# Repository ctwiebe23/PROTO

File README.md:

# NAME

MAKE --- PROTO's embedded python library

# DESCRIPTION

MAKE is Python library that runs on top of [CircuitPython][], creating an
interface for controlling sensors and motors connected to an RP2040-based PCB.

[circuitpython]: https://circuitpython.org/

The goal of the project is to create a simple-to-use library that can be
brought into elementary / middle schools and taught with minimal programming
experience on either side --- student *or* teacher.  It prioritizes readability
and simplicity over efficiency, and was designed under many constraints
imposed by the RP2040, CircuitPython, and its intended environment.

```py
import make

left_motor = make.largemotor(port=6)
right_motor = make.largemotor(port=7, direction=-1)
my_robot = make.drivetrain(left_motor, right_motor)

stop_button = make.button(port=8)

my_robot.drive(100)
make.wait_until(stop_button.pressed)
my_robot.stop()
```

# FUNCTIONS AND CLASSES

# INSTALL

MAKE must be installed on a system that already has CircuitPython set up. If
this is not the case, first follow this guide to [install
CircuitPython][install-circuitpython] on your board.  To determine if
CircuitPython has been installed, plug the board into your computer via a USB
--- the board should pop up in your file system as a USB device named
`CIRCUITPY`.

[install-circuitpython]: https://learn.adafruit.com/welcome-to-circuitpython/installing-circuitpython

Once CircuitPython is working and you have found the `CIRCUITPY` drive, enter
it and copy the `./src/lib` folder from this Github repository to the drive.
This folder (`CIRCUITPY/lib`) is where CircuitPython searches for libraries,
and the `./src/lib` folder in the repo contains everything MAKE needs ---
well, almost.

Depending on your board, additional libraries may need to be installed ---
these can be found in `./src/component_libraries`.  The only such library that
is currently needed is the Adafruit motor library --- if your board is the
[MakerPI RP2040][makerpi], this comes pre-installed, but otherwise you likely
will need to copy `./src/component_libraries/adafruit_motor` into
`CIRCUITPY/lib`.

[makerpi]: https://www.cytron.io/p-maker-pi-rp2040-simplifying-robotics-with-raspberry-pi-rp2040

The final step to get code running is to place a `main.py` file at the root of
`CIRCUITPY`.  This is the file that CircuitPython will run when the board
starts up, and is where you will write the "main method" for your program.  To
upload a new program, simply overwrite `CIRCUITPY/main.py`.

# EXAMPLES

# INDEX

CHANGELOG.md
:   foo

justfile
:   foo

LICENSE
:   foo

pyproject.toml
:   foo

README.md
:   This file.

data/
:   foo

doc/
:   foo

    fonts.html
    :   foo

    pandoc.yml
    :   foo

    source.md
    :   foo

    styles.css
    :   foo

    www/
    :   foo

    tutorial_pages/
    :   foo

        example_code/
        :   foo

src/
:   foo

    main.py
    :   foo

    component_libraries/
    :   foo

    lib/
    :   foo

        make.py
        :   foo

        proto/
        :   foo

            \*/\_\_init\_\_.py
            :   foo

            system.py
            :   foo

            general/
            :   foo

            input/
            :   foo

            motion/
            :   foo

            schemata/
            :   foo

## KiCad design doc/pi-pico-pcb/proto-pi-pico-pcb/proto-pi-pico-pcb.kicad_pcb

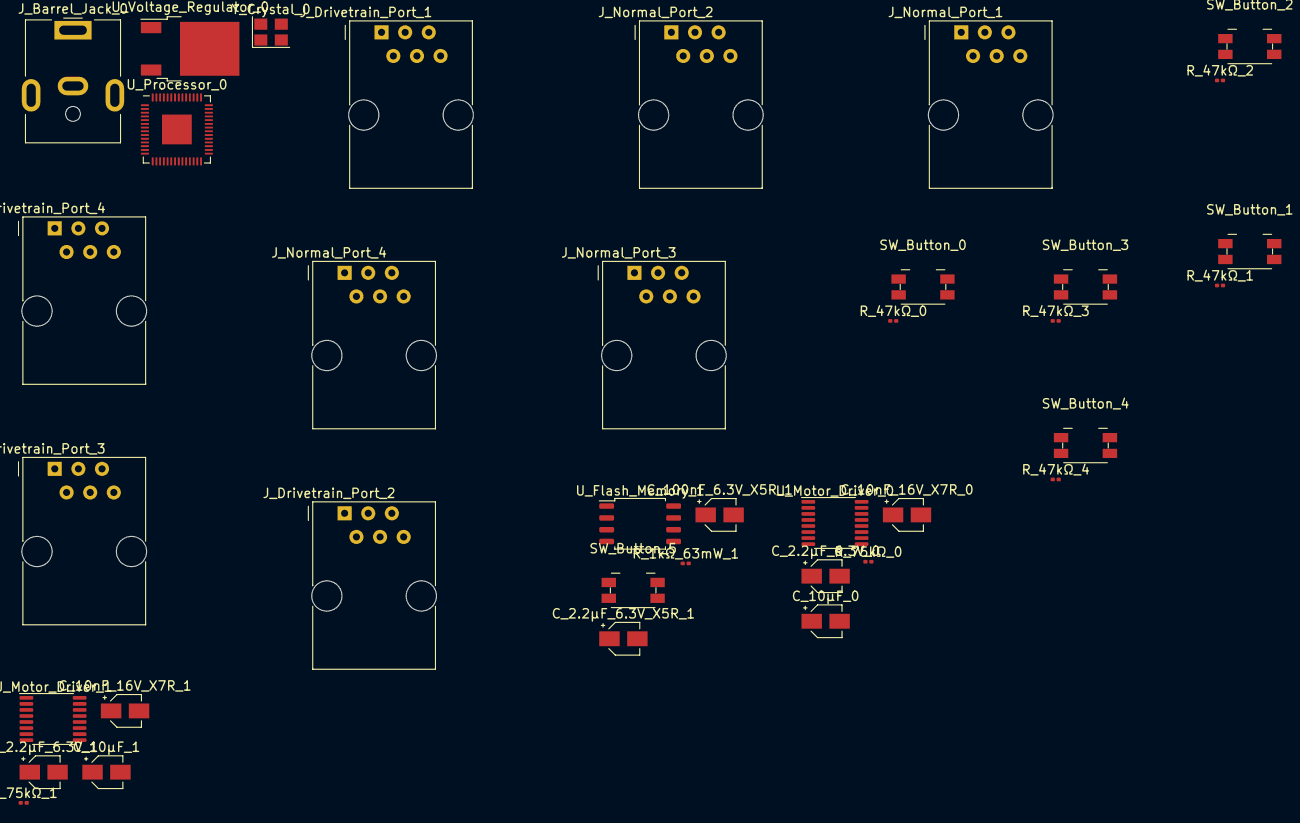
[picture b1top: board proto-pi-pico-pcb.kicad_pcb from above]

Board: 2 copper layers, 37 parts (0 on the bottom side), 52 nets, no tracks yet.

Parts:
C_2.2μF_6.3V_0, C_2.2μF_6.3V_1, C_2.2μF_6.3V_X5R_1, C_10nF_16V_X7R_0, C_10nF_16V_X7R_1, C_10μF_0, C_10μF_1, C_100nF_6.3V_X5R_1: C; CP_Elec_3x5.3
J_Barrel_Jack_0: Barrel_Jack_MountingPin; BarrelJack_CUI_PJ-063AH_Horizontal
J_Drivetrain_Port_1, J_Drivetrain_Port_2, J_Drivetrain_Port_3, J_Drivetrain_Port_4: 6P6C; RJ12_Amphenol_54601
J_Normal_Port_1, J_Normal_Port_2, J_Normal_Port_3, J_Normal_Port_4: 6P6C; RJ12_Amphenol_54601
R_1kΩ_63mW_1, R_47kΩ_0, R_47kΩ_1, R_47kΩ_2, R_47kΩ_3, R_47kΩ_4, R_75kΩ_0, R_75kΩ_1: R; R_0201_0603Metric
SW_Button_0, SW_Button_1, SW_Button_2, SW_Button_3, SW_Button_4, SW_Button_5: SW_Push; Panasonic_EVQPUJ_EVQPUA
U_Flash_Memory_1: W25Q32JVSS; SOIC-8_5.23x5.23mm_P1.27mm
U_Motor_Driver_0, U_Motor_Driver_1: DRV8833PW; TSSOP-16_4.4x5mm_P0.65mm
U_Processor_0: RP2040; QFN-56-1EP_7x7mm_P0.4mm_EP3.2x3.2mm
U_Voltage_Regulator_0: KA78M05_TO252; TO-252-2
Y_Crystal_0: Crystal; Crystal_SMD_Abracon_ABM8G-4Pin_3.2x2.5mm

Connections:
+3.3V: C_2.2μF_6.3V_X5R_1.2, C_100nF_6.3V_X5R_1.2, J_Drivetrain_Port_1.2, J_Drivetrain_Port_2.2, J_Drivetrain_Port_3.2, J_Drivetrain_Port_4.2, J_Normal_Port_1.2, J_Normal_Port_2.2, J_Normal_Port_3.2, J_Normal_Port_4.2, R_47kΩ_0.1, R_47kΩ_1.1, R_47kΩ_2.1, R_47kΩ_3.1, R_47kΩ_4.1, U_Flash_Memory_1.8 (VCC), U_Processor_0.1 (IOVDD), U_Processor_0.10 (IOVDD), U_Processor_0.22 (IOVDD), U_Processor_0.33 (IOVDD), U_Processor_0.42 (IOVDD), U_Processor_0.43 (ADC_AVDD), U_Processor_0.44 (VREG_IN), U_Processor_0.48 (USB_VDD), U_Processor_0.49 (IOVDD), U_Voltage_Regulator_0.3 (VO)
+9V: C_10nF_16V_X7R_0.1, C_10nF_16V_X7R_1.1, C_10μF_0.1, C_10μF_1.1, J_Barrel_Jack_0.1, R_75kΩ_0.1, R_75kΩ_1.1, U_Motor_Driver_0.12 (VM), U_Motor_Driver_1.12 (VM), U_Voltage_Regulator_0.1 (VI)
/Drivetrain_Port_0/DC_0: J_Drivetrain_Port_4.5, U_Motor_Driver_0.2 (AOUT1)
/Drivetrain_Port_0/DC_1: J_Drivetrain_Port_4.6, U_Motor_Driver_0.4 (AOUT2)
/Drivetrain_Port_1/DC_0: J_Drivetrain_Port_1.5, U_Motor_Driver_0.7 (BOUT1)
/Drivetrain_Port_1/DC_1: J_Drivetrain_Port_1.6, U_Motor_Driver_0.5 (BOUT2)
/Drivetrain_Port_2/DC_0: J_Drivetrain_Port_3.5, U_Motor_Driver_1.2 (AOUT1)
/Drivetrain_Port_2/DC_1: J_Drivetrain_Port_3.6, U_Motor_Driver_1.4 (AOUT2)
/Drivetrain_Port_3/DC_0: J_Drivetrain_Port_2.5, U_Motor_Driver_1.7 (BOUT1)
/Drivetrain_Port_3/DC_1: J_Drivetrain_Port_2.6, U_Motor_Driver_1.5 (BOUT2)
/Flash_Memory_0/!CS: R_1kΩ_63mW_1.2, U_Flash_Memory_1.1 (~CS), U_Processor_0.56 (QSPI_SS)
/Flash_Memory_0/CLK: U_Flash_Memory_1.6 (CLK), U_Processor_0.52 (QSPI_SCLK)
/Flash_Memory_0/IO_0: U_Flash_Memory_1.5 (DI(IO0)), U_Processor_0.53 (QSPI_SD0)
/Flash_Memory_0/IO_1: U_Flash_Memory_1.2 (DO(IO1)), U_Processor_0.55 (QSPI_SD1)
/Flash_Memory_0/IO_2: U_Flash_Memory_1.3 (IO2), U_Processor_0.54 (QSPI_SD2)
/Flash_Memory_0/IO_3: U_Flash_Memory_1.7 (IO3), U_Processor_0.51 (QSPI_SD3)
/GP_0: R_47kΩ_0.2, SW_Button_0.2, U_Processor_0.37 (GPIO25)
/GP_1: R_47kΩ_1.2, SW_Button_1.2, U_Processor_0.36 (GPIO24)
/GP_2: R_47kΩ_2.2, SW_Button_2.2, U_Processor_0.35 (GPIO23)
/GP_3: R_47kΩ_3.2, SW_Button_3.2, U_Processor_0.34 (GPIO22)
/GP_4: J_Normal_Port_1.4, U_Processor_0.32 (GPIO21)
/GP_5: J_Normal_Port_2.4, U_Processor_0.31 (GPIO20)
/GP_6: J_Normal_Port_3.4, U_Processor_0.30 (GPIO19)
/GP_7: J_Normal_Port_4.4, U_Processor_0.29 (GPIO18)
/GP_8: J_Drivetrain_Port_4.3, U_Processor_0.28 (GPIO17)
/GP_9: J_Drivetrain_Port_4.4, U_Processor_0.27 (GPIO16)
/GP_10: J_Drivetrain_Port_1.3, U_Processor_0.18 (GPIO15)
/GP_11: J_Drivetrain_Port_1.4, U_Processor_0.17 (GPIO14)
/GP_12: J_Drivetrain_Port_3.3, U_Processor_0.16 (GPIO13)
/GP_13: J_Drivetrain_Port_3.4, U_Processor_0.15 (GPIO12)
/GP_14: J_Drivetrain_Port_2.3, U_Processor_0.14 (GPIO11)
/GP_15: J_Drivetrain_Port_2.4, U_Processor_0.13 (GPIO10)
/Motor_Driver_0/A_IN_0: U_Motor_Driver_0.16 (AIN1), U_Processor_0.12 (GPIO9)
/Motor_Driver_0/A_IN_1: U_Motor_Driver_0.15 (AIN2), U_Processor_0.11 (GPIO8)
/Motor_Driver_0/B_IN_0: U_Motor_Driver_0.9 (BIN1), U_Processor_0.9 (GPIO7)
/Motor_Driver_0/B_IN_1: U_Motor_Driver_0.10 (BIN2), U_Processor_0.8 (GPIO6)
/Motor_Driver_1/A_IN_0: U_Motor_Driver_1.16 (AIN1), U_Processor_0.7 (GPIO5)
/Motor_Driver_1/A_IN_1: U_Motor_Driver_1.15 (AIN2), U_Processor_0.6 (GPIO4)
/Motor_Driver_1/B_IN_0: U_Motor_Driver_1.9 (BIN1), U_Processor_0.5 (GPIO3)
/Motor_Driver_1/B_IN_1: U_Motor_Driver_1.10 (BIN2), U_Processor_0.4 (GPIO2)
/RESET_Button_0/SIGNAL: R_47kΩ_4.2, SW_Button_4.2, U_Processor_0.26 (RUN)
GND: C_2.2μF_6.3V_0.1, C_2.2μF_6.3V_1.1, C_2.2μF_6.3V_X5R_1.1, C_10μF_0.2, C_10μF_1.2, C_100nF_6.3V_X5R_1.1, J_Barrel_Jack_0.2, J_Drivetrain_Port_1.1, J_Drivetrain_Port_2.1, J_Drivetrain_Port_3.1, J_Drivetrain_Port_4.1, J_Normal_Port_1.1, J_Normal_Port_2.1, J_Normal_Port_3.1, J_Normal_Port_4.1, SW_Button_0.1, SW_Button_1.1, SW_Button_2.1, SW_Button_3.1, SW_Button_4.1, SW_Button_5.2, U_Flash_Memory_1.4 (GND), U_Motor_Driver_0.3 (AISEN), U_Motor_Driver_0.6 (BISEN), U_Motor_Driver_0.13 (GND), U_Motor_Driver_1.3 (AISEN), U_Motor_Driver_1.6 (BISEN), U_Motor_Driver_1.13 (GND), U_Processor_0.19 (TESTEN), U_Processor_0.57 (GND), U_Voltage_Regulator_0.2 (GND)
unnamed: C_2.2μF_6.3V_0.2, U_Motor_Driver_0.14 (VINT)
unnamed: C_2.2μF_6.3V_1.2, U_Motor_Driver_1.14 (VINT)
unnamed: C_10nF_16V_X7R_0.2, U_Motor_Driver_0.11 (VCP)
unnamed: C_10nF_16V_X7R_1.2, U_Motor_Driver_1.11 (VCP)
unnamed: R_1kΩ_63mW_1.1, SW_Button_5.1
unnamed: R_75kΩ_0.2, U_Motor_Driver_0.1 (nSLEEP)
unnamed: R_75kΩ_1.2, U_Motor_Driver_1.1 (nSLEEP)
unnamed: U_Processor_0.20 (XIN), Y_Crystal_0.1
unnamed: U_Processor_0.21 (XOUT), Y_Crystal_0.2
unnamed: U_Processor_0.23 (DVDD), U_Processor_0.45 (VREG_VOUT), U_Processor_0.50 (DVDD)

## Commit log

2024-03-21 created utility file
2024-03-27 changed to class structure
2024-03-30 formatting
2024-04-05 created pause_until and changed formatting
2024-04-05 started documentation
2024-04-05 setup readme pages
2024-04-06 tweaking of formatting
2024-04-10 declaring as of yet unused variables
2024-04-11 established good practice
2024-04-11 testing git log
2024-04-16 redid download link
2024-04-16 undid prev change
2024-04-17 documentation
2024-04-17 filled out readme and formatted pages
2024-04-17 fixed Callable error
2024-04-17 renamed dc to motor
2024-04-17 victor demo
2024-04-17 04/17 meeting
2024-04-17 naming convention
2024-04-17 fixed error
2024-04-18 added largemotor.stop
2024-04-18 removed whitespace
2024-04-22 documentation work
2024-04-22 setting up stopall
2024-04-22 translated techdoc to markdown
2024-04-25 begun transfer from md to tex
2024-04-29 cleaned up
2024-04-29 added todo and stl's
2024-04-29 translated techdoc to latex for real this time
2024-04-29 added MaKeTeX.sh
2024-05-01 finished servo
2024-05-03 rearranging
2024-05-08 documentation preparation
2024-05-08 fixed typo
2024-05-08 folder restructering
2024-05-08 added grove ports
2024-05-08 structering
2024-05-09 3d printed insert tester
2024-05-09 little bit of expirementing
2024-05-09 typo
2024-05-09 reorganized file structure to reflect pi
2024-05-09 fixed regex issue
2024-05-09 updated todo
2024-05-09 covered edge case
2024-05-11 removed will
2024-05-13 updated prints and renamed folders
2024-05-14 finished drivetrain, configured presentation code
2024-05-14 made presentation code
2024-05-16 presentation practice
2024-05-16 final presentation change
2024-05-21 added additional todo
2024-06-04 gave drivetrain alt constructors and revamped BAPCAT warning
2024-06-04 added to todo
2024-06-04 reformatting
2024-06-04 cleaned whitespace
2024-06-05 formating
2024-06-23 restructured BAPCAT to limit cat abuse
2024-06-30 cleared whitespace
2024-07-05 redid bapcat
2024-07-19 refactoring BAPCAT
2024-07-19 held BAPCAT to a higher standard
2024-07-20 renamed motors + drivetrain
2024-07-20 major reformatting and proofreading
2024-07-21 documented small_motor
2024-07-24 removec camelCasing
2024-07-24 BAPCAT now supports directories
2024-08-01 restructered src folder
2024-08-13 added start-up script to make
2024-08-23 restructured project to eliminate bapcat
2024-08-23 wrote out vocab list
2024-08-23 tested right motor
2024-08-27 bound function
2024-08-29 finished speed_bounder
2024-08-30 implemented bound_speed
2024-09-01 whitespace
2024-09-03 bounded motor speeds
2024-09-07 lesson plan musings
2024-09-23 demo project
2024-10-01 created empty sonar file
2024-10-07 updated code example
2024-10-08 added common mistakes
2024-10-12 tested generated code
2024-10-18 added led functions (untested)
2024-10-18 renamed speed to power
2024-10-18 converted led to class
2024-10-20 Create LED test
2024-10-20 Update led test
2024-10-20 Rename led test to led test.py
2024-10-23 redid techdoc
2024-10-23 built techdoc
2024-10-23 generated DOCX and HTML with PDF
2024-10-23 fixed type and reformatted abstract
2024-10-24 stopped generating .HTML and .DOCX
2024-10-25 tested servos on grove ports
2024-10-31 new prints
2024-11-04 removed leds and changed ports
2024-11-04 updated documentation
2024-11-04 built docx and html
2024-11-08 created demo program for first focus group
2024-11-08 new main program
2024-11-09 redid demo program
2024-11-12 added delay
2024-11-19 prepping for use of schemata
2024-11-19 changed default values
2024-11-19 further set up schema
2024-11-20 attempted to implement interrupts and successfully implemented schema
2024-11-20 updated main
2024-11-20 changed var name
2024-11-28 added wait_until back to the public exports
2024-12-02 updated demo
2024-12-02 documented main
2024-12-07 reconfigured held buttons, added wait_while, and renamed system components
2025-01-03 working on IR sensor
2025-02-04 prepped for pi pico
2025-02-06 Line Editor Update
    Added Copy and Save buttons. Debugged line coder.
2025-02-06 cleaned up mis-commit
2025-02-10 changed cservo range
2025-02-16 restored MAKERPI as default schema
2025-02-18 new main
2025-02-25 implemented servos
2025-02-25 making documentation
2025-03-04 fixed bug in FSR90 schema power scaler
2025-03-10 combined drift and direction in drivetrains
2025-03-13 moved component libraries out of main lib folder
2025-03-27 drive backwards with dedicated methods
2025-03-30 tractor drive code
2025-04-01 began pi pico techdoc
2025-04-08 formatted files with black and started documentation for pi pico
2025-04-15 got servo running on pi pico
2025-04-23 started work on PCB
2025-04-23 added grounds
2025-04-24 added bypass capacitors
2025-07-20 wired up external ports to bus
2025-07-21 added general barrel jack
2025-08-06 gave general parts temporary footprints
2025-08-26 removed dead pins on rp2040
2025-08-27 added 2 new drivetrain ports, 2nd driver, and push buttons
2025-08-30 moved SYSTEM from general/system_specs.py to system.py; added TODO.txt
2025-08-30 added tasks to TODO
2025-08-30 formatted code
2025-09-04 introduced nested sheets
2025-09-07 converted ports to nested sheets
2025-09-08 formatted schematic
2025-09-10 added flash memory
2025-09-11 gave demo
2025-09-11 moved pcb to dedicated repo and cleaned old documentation
2025-09-11 cleared old docs
2025-09-11 added docstring
2025-09-13 begun redoing documentation
2025-09-13 updated setup page
2025-10-31 changed default cservo stop value
2025-12-01 changes from presi practice
2026-02-25 prepping for n20 test
2026-02-26 added default buttons and leds
2026-02-26 n20 working on protoboard
2026-03-05 renamed dc schema to driver schema
2026-03-05 renamed motors
2026-03-25 added uf2s, mapped proper PROTOBOARD ports
2026-03-26 removed GP29 until custom uf2 is built
2026-03-31 untested demo code for the dr. j presentation
2026-04-04 testing n20s with demo
2026-04-14 Update port numbers and add new servo support
2026-04-14 added new servo schema, reordered ports
2026-04-16 renamed motors to old vocab
